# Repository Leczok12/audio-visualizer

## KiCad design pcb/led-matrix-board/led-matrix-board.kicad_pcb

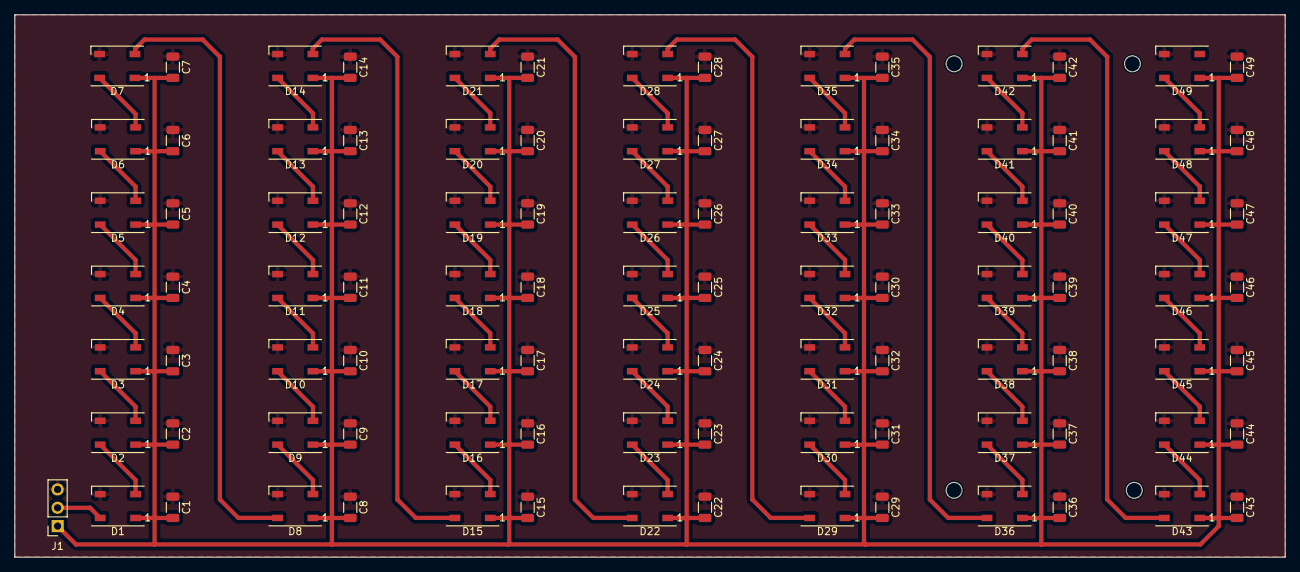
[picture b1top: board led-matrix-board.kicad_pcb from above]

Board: 2 copper layers, 176.0 x 75.1 mm, 99 parts (0 on the bottom side), 51 nets.

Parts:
C1, C2, C3, C4, C5, C6, C7, C8, C9, C10, C11, C12, C13, C14, C15, C16, C17, C18, C19, C20, C21, C22, C23, C24, C25, C26, C27, C28, C29, C30, C31, C32, C33, C34, C35, C36, C37, C38, C39, C40, C41, C42, C43, C44, C45, C46, C47, C48, C49: 100nF; C_1206_3216Metric
D1, D2, D3, D4, D5, D6, D7, D8, D9, D10, D11, D12, D13, D14, D15, D16, D17, D18, D19, D20, D21, D22, D23, D24, D25, D26, D27, D28, D29, D30, D31, D32, D33, D34, D35, D36, D37, D38, D39, D40, D41, D42, D43, D44, D45, D46, D47, D48, D49: WS2812B; LED_WS2812B_PLCC4_5.0x5.0mm_P3.2mm
J1: Conn_01x03; PinSocket_1x03_P2.54mm_Vertical

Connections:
5V: C1.2, C2.2, C3.2, C4.2, C5.2, C6.2, C7.2, C8.2, C9.2, C10.2, C11.2, C12.2, C13.2, C14.2, C15.2, C16.2, C17.2, C18.2, C19.2, C20.2, C21.2, C22.2, C23.2, C24.2, C25.2, C26.2, C27.2, C28.2, C29.2, C30.2, C31.2, C32.2, C33.2, C34.2, C35.2, C36.2, C37.2, C38.2, C39.2, C40.2, C41.2, C42.2, C43.2, C44.2, C45.2, C46.2, C47.2, C48.2, C49.2, D1.1 (VDD), D2.1 (VDD), D3.1 (VDD), D4.1 (VDD), D5.1 (VDD), D6.1 (VDD), D7.1 (VDD), D8.1 (VDD), D9.1 (VDD), D10.1 (VDD), D11.1 (VDD), D12.1 (VDD), D13.1 (VDD), D14.1 (VDD), D15.1 (VDD), D16.1 (VDD), D17.1 (VDD), D18.1 (VDD), D19.1 (VDD), D20.1 (VDD), D21.1 (VDD), D22.1 (VDD), D23.1 (VDD), D24.1 (VDD), D25.1 (VDD), D26.1 (VDD), D27.1 (VDD), D28.1 (VDD), D29.1 (VDD), D30.1 (VDD), D31.1 (VDD), D32.1 (VDD), D33.1 (VDD), D34.1 (VDD), D35.1 (VDD), D36.1 (VDD), D37.1 (VDD), D38.1 (VDD), D39.1 (VDD), D40.1 (VDD), D41.1 (VDD), D42.1 (VDD), D43.1 (VDD), D44.1 (VDD), D45.1 (VDD), D46.1 (VDD), D47.1 (VDD), D48.1 (VDD), D49.1 (VDD), J1.1
DIN: D1.4 (DIN), J1.2
GND: C1.1, C2.1, C3.1, C4.1, C5.1, C6.1, C7.1, C8.1, C9.1, C10.1, C11.1, C12.1, C13.1, C14.1, C15.1, C16.1, C17.1, C18.1, C19.1, C20.1, C21.1, C22.1, C23.1, C24.1, C25.1, C26.1, C27.1, C28.1, C29.1, C30.1, C31.1, C32.1, C33.1, C34.1, C35.1, C36.1, C37.1, C38.1, C39.1, C40.1, C41.1, C42.1, C43.1, C44.1, C45.1, C46.1, C47.1, C48.1, C49.1, D1.3 (VSS), D2.3 (VSS), D3.3 (VSS), D4.3 (VSS), D5.3 (VSS), D6.3 (VSS), D7.3 (VSS), D8.3 (VSS), D9.3 (VSS), D10.3 (VSS), D11.3 (VSS), D12.3 (VSS), D13.3 (VSS), D14.3 (VSS), D15.3 (VSS), D16.3 (VSS), D17.3 (VSS), D18.3 (VSS), D19.3 (VSS), D20.3 (VSS), D21.3 (VSS), D22.3 (VSS), D23.3 (VSS), D24.3 (VSS), D25.3 (VSS), D26.3 (VSS), D27.3 (VSS), D28.3 (VSS), D29.3 (VSS), D30.3 (VSS), D31.3 (VSS), D32.3 (VSS), D33.3 (VSS), D34.3 (VSS), D35.3 (VSS), D36.3 (VSS), D37.3 (VSS), D38.3 (VSS), D39.3 (VSS), D40.3 (VSS), D41.3 (VSS), D42.3 (VSS), D43.3 (VSS), D44.3 (VSS), D45.3 (VSS), D46.3 (VSS), D47.3 (VSS), D48.3 (VSS), D49.3 (VSS), J1.3
unnamed: D1.2 (DOUT), D2.4 (DIN)
unnamed: D2.2 (DOUT), D3.4 (DIN)
unnamed: D3.2 (DOUT), D4.4 (DIN)
unnamed: D4.2 (DOUT), D5.4 (DIN)
unnamed: D5.2 (DOUT), D6.4 (DIN)
unnamed: D6.2 (DOUT), D7.4 (DIN)
unnamed: D7.2 (DOUT), D8.4 (DIN)
unnamed: D8.2 (DOUT), D9.4 (DIN)
unnamed: D9.2 (DOUT), D10.4 (DIN)
unnamed: D10.2 (DOUT), D11.4 (DIN)
unnamed: D11.2 (DOUT), D12.4 (DIN)
unnamed: D12.2 (DOUT), D13.4 (DIN)
unnamed: D13.2 (DOUT), D14.4 (DIN)
unnamed: D14.2 (DOUT), D15.4 (DIN)
unnamed: D15.2 (DOUT), D16.4 (DIN)
unnamed: D16.2 (DOUT), D17.4 (DIN)
unnamed: D17.2 (DOUT), D18.4 (DIN)
unnamed: D18.2 (DOUT), D19.4 (DIN)
unnamed: D19.2 (DOUT), D20.4 (DIN)
unnamed: D20.2 (DOUT), D21.4 (DIN)
unnamed: D21.2 (DOUT), D22.4 (DIN)
unnamed: D22.2 (DOUT), D23.4 (DIN)
unnamed: D23.2 (DOUT), D24.4 (DIN)
unnamed: D24.2 (DOUT), D25.4 (DIN)
unnamed: D25.2 (DOUT), D26.4 (DIN)
unnamed: D26.2 (DOUT), D27.4 (DIN)
unnamed: D27.2 (DOUT), D28.4 (DIN)
unnamed: D28.2 (DOUT), D29.4 (DIN)
unnamed: D29.2 (DOUT), D30.4 (DIN)
unnamed: D30.2 (DOUT), D31.4 (DIN)
unnamed: D31.2 (DOUT), D32.4 (DIN)
unnamed: D32.2 (DOUT), D33.4 (DIN)
unnamed: D33.2 (DOUT), D34.4 (DIN)
unnamed: D34.2 (DOUT), D35.4 (DIN)
unnamed: D35.2 (DOUT), D36.4 (DIN)
unnamed: D36.2 (DOUT), D37.4 (DIN)
unnamed: D37.2 (DOUT), D38.4 (DIN)
unnamed: D38.2 (DOUT), D39.4 (DIN)
unnamed: D39.2 (DOUT), D40.4 (DIN)
unnamed: D40.2 (DOUT), D41.4 (DIN)
unnamed: D41.2 (DOUT), D42.4 (DIN)
unnamed: D42.2 (DOUT), D43.4 (DIN)
unnamed: D43.2 (DOUT), D44.4 (DIN)
unnamed: D44.2 (DOUT), D45.4 (DIN)
unnamed: D45.2 (DOUT), D46.4 (DIN)
unnamed: D46.2 (DOUT), D47.4 (DIN)
unnamed: D47.2 (DOUT), D48.4 (DIN)
unnamed: D48.2 (DOUT), D49.4 (DIN)

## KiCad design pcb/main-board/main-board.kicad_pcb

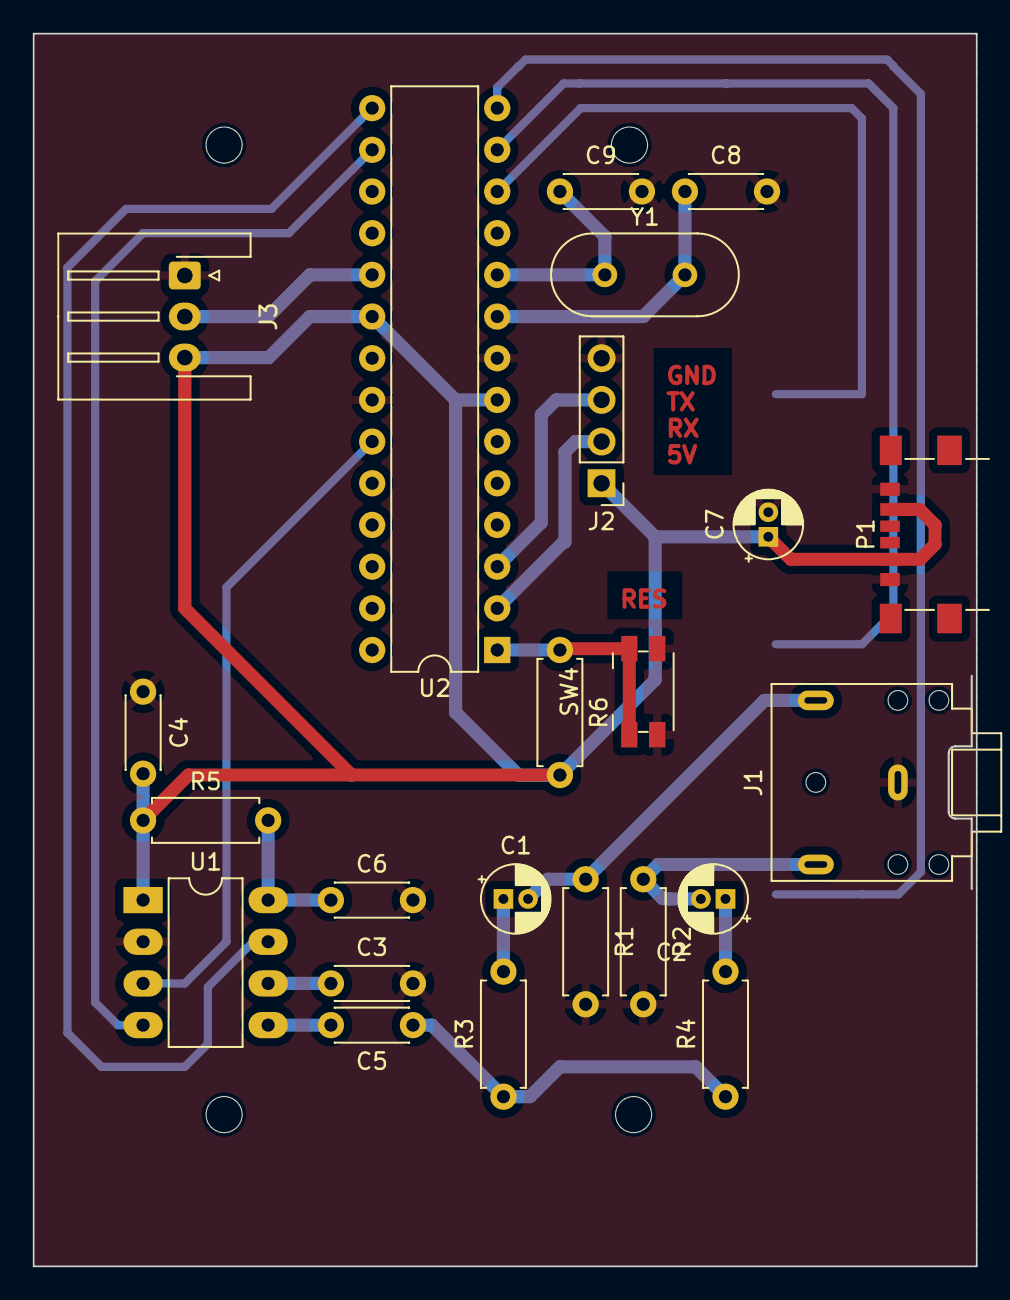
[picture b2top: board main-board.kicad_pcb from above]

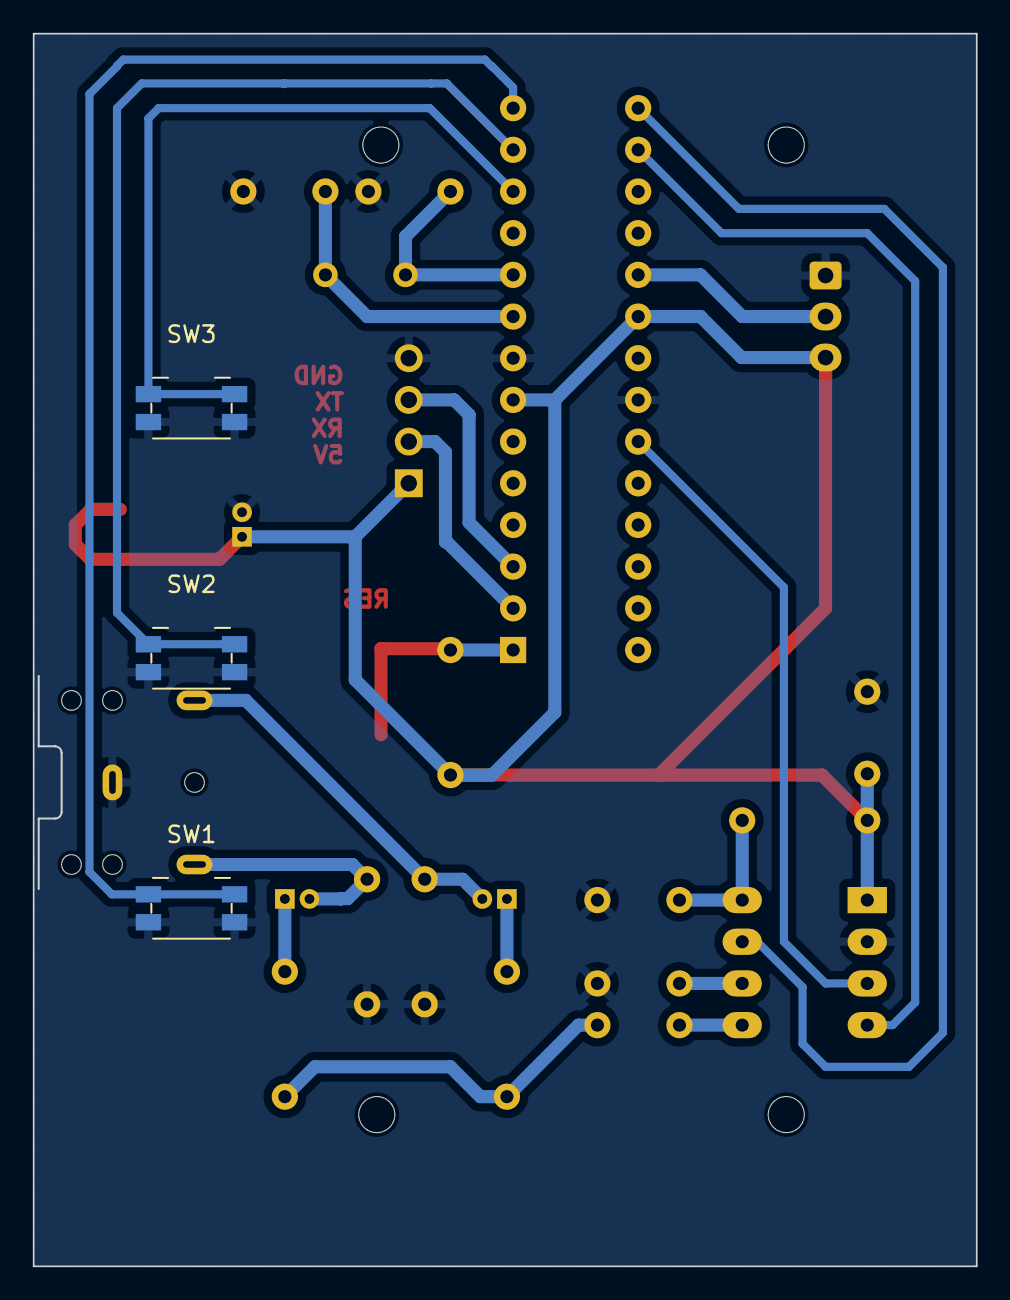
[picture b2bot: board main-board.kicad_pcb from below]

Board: 2 copper layers, 57.5 x 75.1 mm, 26 parts (3 on the bottom side), 22 nets.

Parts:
C1, C2, C7: 10uf; CP_Radial_D4.0mm_P1.50mm
C3, C4, C5: 0.1uF; C_Disc_D4.3mm_W1.9mm_P5.00mm
C6: 33pF; C_Disc_D4.3mm_W1.9mm_P5.00mm
C8, C9: 22pF; C_Disc_D4.3mm_W1.9mm_P5.00mm
J1: IN_1; Jack_3.5mm_CUI_SJ1-3523N_Horizontal
J2: Conn_01x04; PinHeader_1x04_P2.54mm_Vertical
J3: Conn_01x03; JST_XH_S3B-XH-A-1_1x03_P2.50mm_Horizontal
P1: USB_C_Plug_USB2.0; USB_C_Receptacle_GCT_USB4135-GF-A_6P_TopMnt_Horizontal
R1, R2: 100K; R_Axial_DIN0207_L6.3mm_D2.5mm_P7.62mm_Horizontal
R3, R4: 22K; R_Axial_DIN0207_L6.3mm_D2.5mm_P7.62mm_Horizontal
R5: 220K; R_Axial_DIN0207_L6.3mm_D2.5mm_P7.62mm_Horizontal
R6: 10K; R_Axial_DIN0207_L6.3mm_D2.5mm_P7.62mm_Horizontal
SW1, SW2, SW3, SW4: SW_Push; Panasonic_EVQPUJ_EVQPUA
U1: MSGEQ7; DIP-8_W7.62mm_LongPads
U2: ATmega328-P; DIP-28_W7.62mm
Y1: Crystal; Crystal_HC49-4H_Vertical

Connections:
5V: C4.2, C7.1, J2.1, J3.3, P1.A9 (VBUS), P1.B9 (VBUS), R5.1, R6.2, U1.1 (VDD), U2.7 (VCC), U2.20 (AVCC)
GND: C3.2, C4.1, C6.2, C7.2, C8.2, C9.2, J1.S, J2.4, J3.1, P1.A12 (GND), P1.B12 (GND), R1.2, R2.2, SW1.2, SW2.2, SW3.2, SW4.2, U1.2 (VSS), U2.8 (GND), U2.22 (GND)
IN: C5.1, R3.1, R4.1
unnamed: C1.1, R3.2
unnamed: C1.2, J1.T, R1.1
unnamed: C2.1, R4.2
unnamed: C2.2, J1.R, R2.1
unnamed: C6.1, R5.2, U1.8 (CKIN)
unnamed: C3.1, U1.6 (GND)
unnamed: C5.2, U1.5 (IN)
unnamed: C8.1, U2.9 (XTAL1/PB6), Y1.2
unnamed: C9.1, U2.10 (XTAL2/PB7), Y1.1
unnamed: R6.1, SW4.1, U2.1 (~RESET/PC6)
PIN_6: SW3.1, U2.12 (PD6)
PIN_7: SW2.1, U2.13 (PD7)
PIN_8: SW1.1, U2.14 (PB0)
PIN_9: U1.7 (RESET), U2.15 (PB1)
PIN_10: U1.4 (STROBE), U2.16 (PB2)
PIN_13: J3.2, U2.19 (PB5)
PIN_A0: U1.3 (OUT), U2.23 (PC0)
RX: J2.2, U2.2 (PD0)
TX: J2.3, U2.3 (PD1)
